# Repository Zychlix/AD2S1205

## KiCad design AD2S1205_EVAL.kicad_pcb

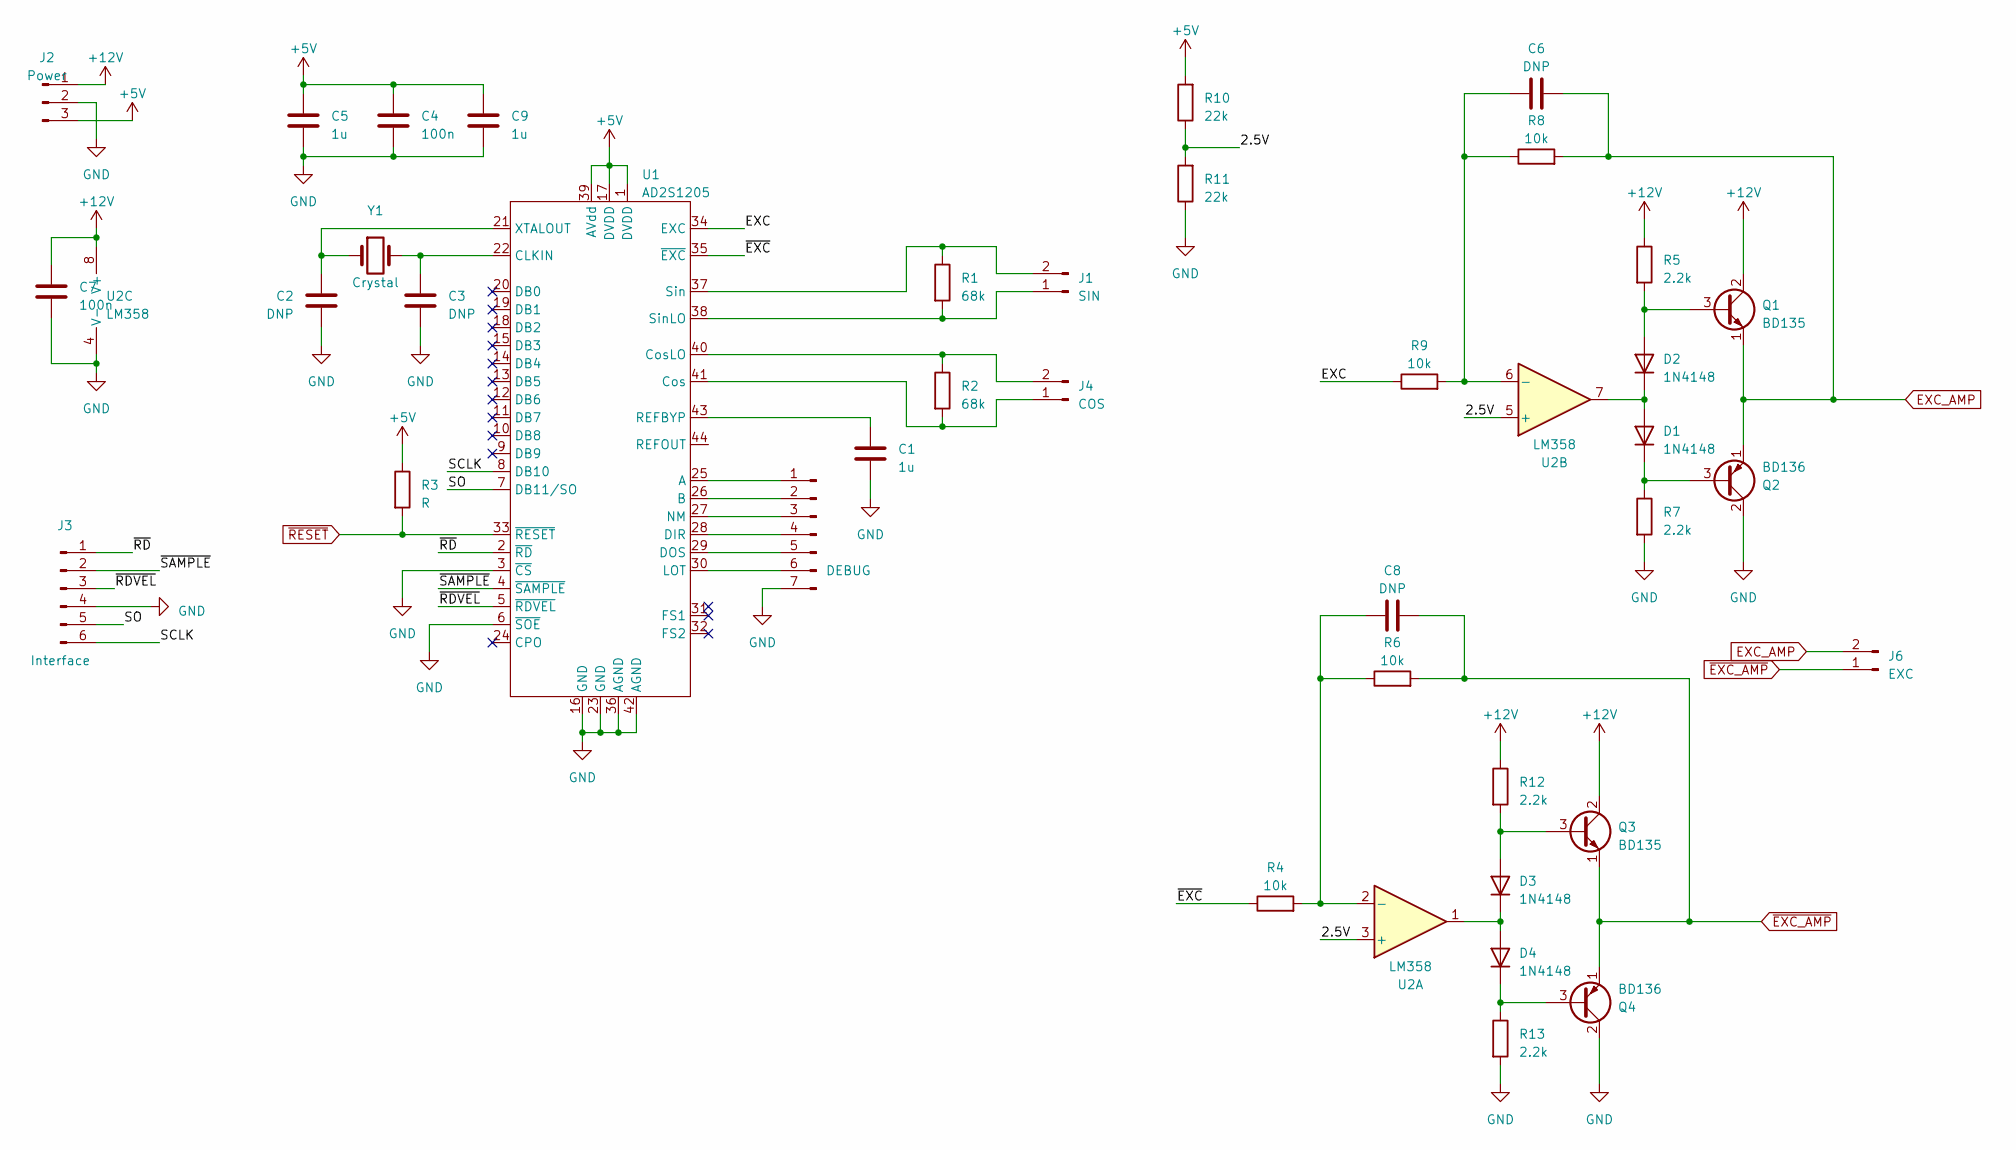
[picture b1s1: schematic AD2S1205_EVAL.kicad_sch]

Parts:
C1, C5, C9: 1u; C_0805_2012Metric_Pad1.18x1.45mm_HandSolder
C2, C3, C6, C8: DNP; C_0805_2012Metric_Pad1.18x1.45mm_HandSolder
C4, C7: 100n; C_0805_2012Metric_Pad1.18x1.45mm_HandSolder
D1, D2, D3, D4: 1N4148; D_SMA_Handsoldering
J1: SIN; PinHeader_1x02_P2.54mm_Vertical
J2: Power; PinHeader_1x03_P2.54mm_Vertical
J3: Interface; PinHeader_1x06_P2.54mm_Vertical
J4: COS; PinHeader_1x02_P2.54mm_Vertical
J5: DEBUG; PinHeader_1x07_P2.54mm_Vertical
J6: EXC; PinHeader_1x02_P2.54mm_Vertical
Q1, Q3: BD135; TO-126-3_Vertical
Q2, Q4: BD136; TO-126-3_Vertical
R1, R2: 68k; R_0805_2012Metric
R3: R; R_0805_2012Metric
R4, R6, R8, R9: 10k; R_0805_2012Metric
R5, R7, R12, R13: 2.2k; R_0805_2012Metric
R10, R11: 22k; R_0805_2012Metric
U1: AD2S1205; LQFP-44_10x10mm_P0.8mm
U2: LM358; SO-8_3.9x4.9mm_P1.27mm
Y1: Crystal; Crystal_HC49-U_Vertical

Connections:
+5V: C4.1, C5.1, C9.1, J2.3, R3.1, R10.2, U1.1 (DVDD), U1.17 (DVDD), U1.39 (AVdd)
+12V: C7.1, J2.1, Q1.2 (C), Q3.2 (C), R5.1, R12.1, U2.8 (V+)
/2.5V: R10.1, R11.2, U2.3 (+), U2.5 (+)
/EXC: R9.1, U1.34 (EXC)
/SCLK: J3.6, U1.8 (DB10)
/SO: J3.5, U1.7 (DB11/SO)
/~EXC: R4.1, U1.35 (~EXC)
/~RDVEL: J3.3, U1.5 (~RDVEL)
/~RD: J3.1, U1.2 (~RD)
/~SAMPLE: J3.2, U1.4 (~SAMPLE)
EXC_AMP: C6.2, J6.2, Q1.1 (E), Q2.1 (E), R8.2
GND: C1.2, C2.2, C3.2, C4.2, C5.2, C7.2, C9.2, J2.2, J3.4, J5.7, Q2.2 (C), Q4.2 (C), R7.2, R11.1, R13.2, U1.3 (~CS), U1.6 (~SOE), U1.16 (GND), U1.23 (GND), U1.36 (AGND), U1.42 (AGND), U2.4 (V-)
unnamed: D1.2 (A), D2.1 (K), U2.7
unnamed: D1.1 (K), Q2.3 (B), R7.1
unnamed: D2.2 (A), Q1.3 (B), R5.2
unnamed: D3.2 (A), Q3.3 (B), R12.2
unnamed: D3.1 (K), D4.2 (A), U2.1
unnamed: D4.1 (K), Q4.3 (B), R13.1
unnamed: J1.1, R1.2, U1.38 (SinLO)
unnamed: J1.2, R1.1, U1.37 (Sin)
unnamed: J4.1, R2.2, U1.41 (Cos)
unnamed: J4.2, R2.1, U1.40 (CosLO)
unnamed: J5.1, U1.25 (A)
unnamed: J5.2, U1.26 (B)
unnamed: J5.3, U1.27 (NM)
unnamed: J5.4, U1.28 (DIR)
unnamed: J5.5, U1.29 (DOS)
unnamed: J5.6, U1.30 (LOT)
unnamed: C3.1, U1.22 (CLKIN), Y1.2
unnamed: C1.1, U1.43 (REFBYP)
unnamed: C2.1, U1.21 (XTALOUT), Y1.1
unnamed: C8.1, R4.2, R6.1, U2.2 (-)
unnamed: C6.1, R8.1, R9.2, U2.6 (-)
~EXC_AMP: C8.2, J6.1, Q3.1 (E), Q4.1 (E), R6.2
~RESET: R3.2, U1.33 (~RESET)

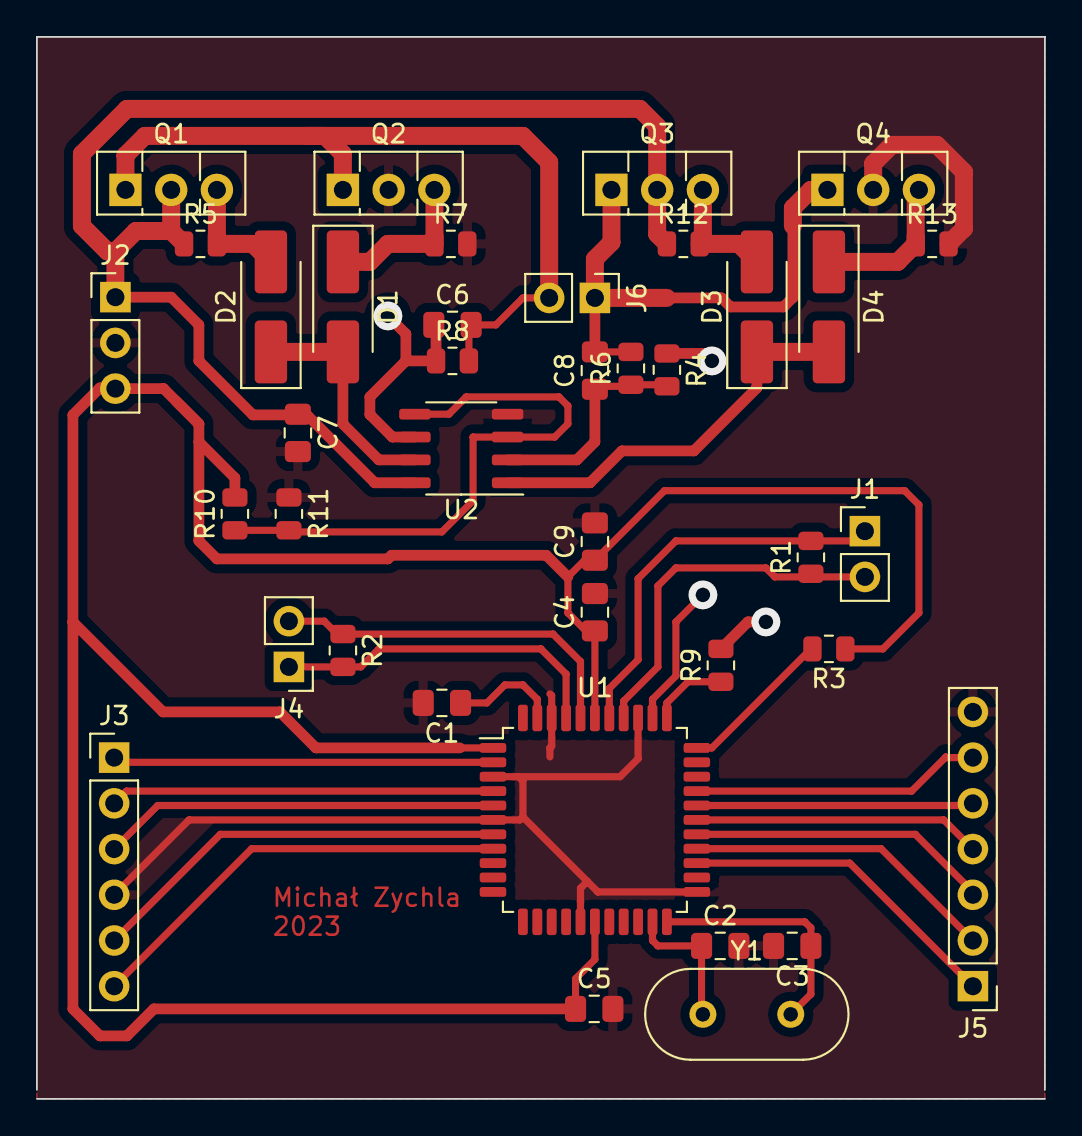
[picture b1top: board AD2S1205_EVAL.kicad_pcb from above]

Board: 2 copper layers, 56.0 x 59.0 mm, 39 parts (0 on the bottom side), 35 nets.

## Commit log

2023-04-13 Sample schematic copied
2023-04-19 Driver schematic done
2023-04-20 Layout
2023-04-21 layout complete
2023-04-22 final
2023-04-22 Middle point repaired, added crossover dist resistors
2023-04-22 added pinout
